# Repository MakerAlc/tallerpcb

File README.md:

# Taller de iniciación a los PCBs de MakerAlc
Repositorio del taller de iniciación a los PCBs impartido en MakerAlc.

En este repositorio se encuentran los archivos necesarios para el desarrollo de cada sesión.

Más información en https://sites.google.com/view/makealc/inicio

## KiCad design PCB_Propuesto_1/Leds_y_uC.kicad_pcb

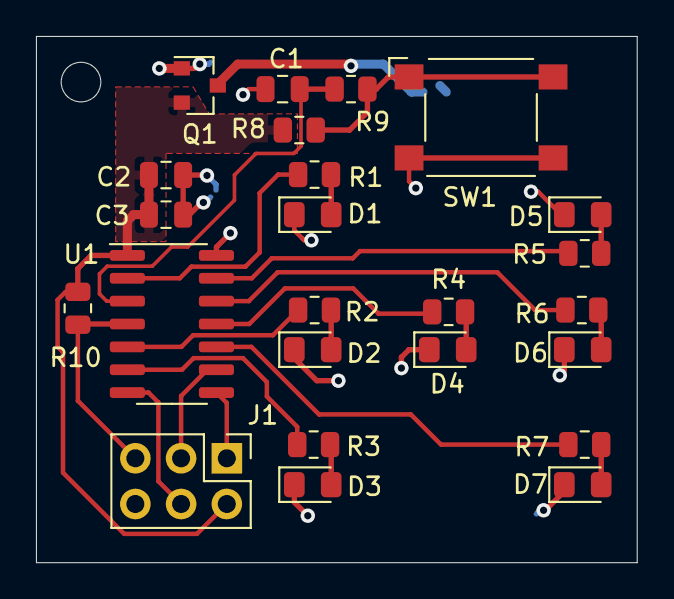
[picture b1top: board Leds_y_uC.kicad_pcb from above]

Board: 2 copper layers, 33.4 x 29.2 mm, 25 parts (1 on the bottom side), 23 nets.

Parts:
BT1: Battery_Cell; BatteryHolder_MPD_BC2003_1x2032
C1, C3: 100 nF; C_0805_2012Metric
C2: 10 uF; C_0805_2012Metric
D1, D2, D3, D4, D5, D6, D7: LED; LED_0805_2012Metric_Pad1.15x1.40mm_HandSolder
J1: AVR-ISP-6; PinHeader_2x03_P2.54mm_Vertical
Q1: Si2319CDS; SOT-23
R1, R2, R3, R4, R5, R6, R7, R9: 360; R_0805_2012Metric
R8, R10: 10K; R_0805_2012Metric
SW1: SW_MEC_5E; SW_SPST_Omron_B3FS-100xP
U1: ATtiny841-SSU; SOIC-14_3.9x8.7mm_P1.27mm

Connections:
GND: BT1.2, C1.2, C2.2, C3.2, D1.1, D2.1, D3.1, D4.1, D5.1, D6.1, D7.1, J1.6, Q1.1, SW1.3, SW1.4, U1.14
LED: R2.1, U1.5
MISO: J1.1, U1.8
MOSI: J1.4, U1.7
unnamed: BT1.1, Q1.3
unnamed: C1.1, R9.2, U1.3
unnamed: D1.2, R1.2
unnamed: D2.2, R2.2
unnamed: D3.2, R3.2
unnamed: D4.2, R4.2
unnamed: D5.2, R5.2
unnamed: D6.2, R6.2
unnamed: D7.2, R7.2
unnamed: R1.1, U1.2
unnamed: R3.1, U1.6
unnamed: R4.1, U1.11
unnamed: R5.1, U1.13
unnamed: R6.1, U1.12
unnamed: R7.1, U1.10
unnamed: R8.1, R9.1, SW1.1, SW1.2
RST: J1.5, R10.1, U1.4
SCK: J1.3, U1.9
VCC: C2.1, C3.1, J1.2, Q1.2, R8.2, R10.2, U1.1

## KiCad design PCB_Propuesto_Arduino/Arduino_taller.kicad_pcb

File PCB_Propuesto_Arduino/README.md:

# Taller_PCB_MakerAlc
Taller de iniciación a los PCBs

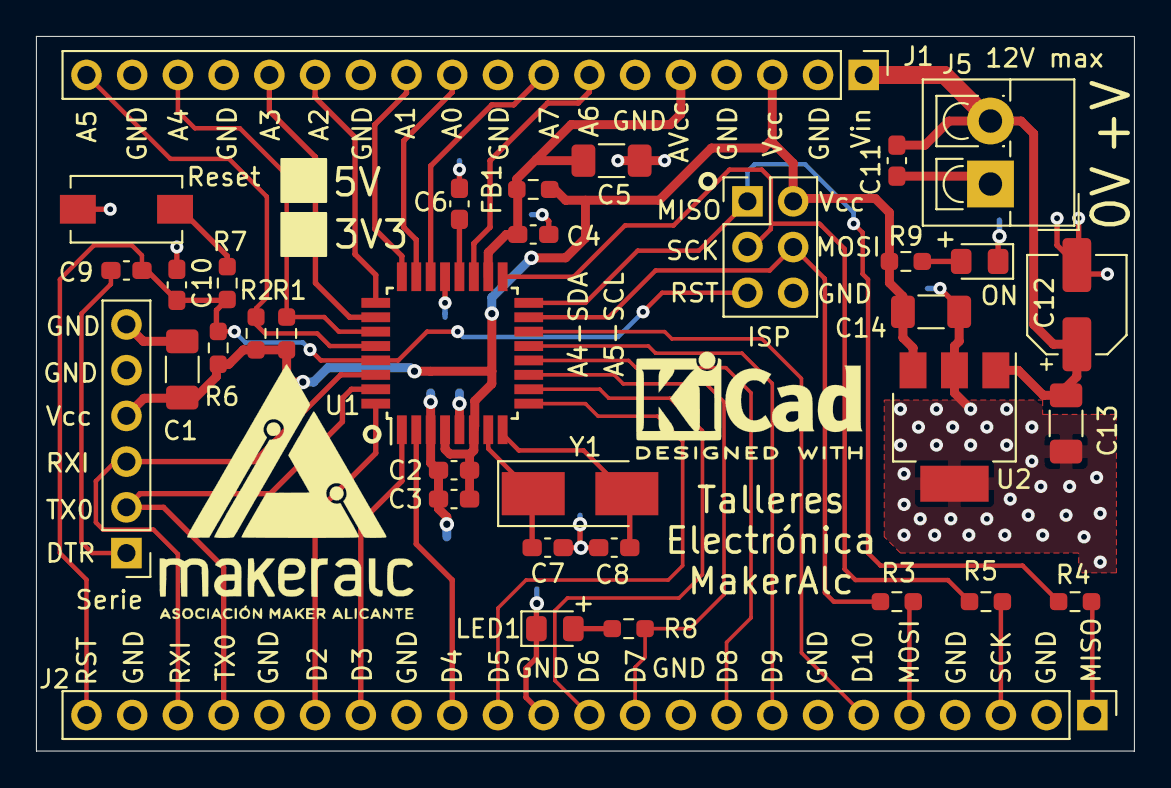
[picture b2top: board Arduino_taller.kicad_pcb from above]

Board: 2 copper layers, 61.0 x 39.7 mm, 35 parts (0 on the bottom side), 37 nets.

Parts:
C1, C5, C13, C14: 10 uF; C_1206_3216Metric_Pad1.33x1.80mm_HandSolder
C2, C3, C4, C6, C9, C11: 100 nF; C_0603_1608Metric_Pad1.08x0.95mm_HandSolder
C7, C8: 16 pF; C_0603_1608Metric_Pad1.08x0.95mm_HandSolder
C10: 10 nF; C_0603_1608Metric_Pad1.08x0.95mm_HandSolder
C12: DNP; CP_Elec_5x5.4
FB1: Ferrite_Bead_Small; R_0603_1608Metric_Pad0.98x0.95mm_HandSolder
ISP: AVR-ISP-6; PinHeader_2x03_P2.54mm_Vertical
J1: Conn_01x18; PinHeader_1x18_P2.54mm_Vertical
J2: Conn_01x23; PinHeader_1x23_P2.54mm_Vertical
J5: Screw_Terminal_01x02; TerminalBlock_4Ucon_1x02_P3.50mm_Vertical
LED1: LED; LED_0805_2012Metric_Pad1.15x1.40mm_HandSolder
ON: LED; LED_0805_2012Metric_Pad1.15x1.40mm_HandSolder
R1, R2: 4k7; R_0603_1608Metric_Pad0.98x0.95mm_HandSolder
R3, R4, R5, R8, R9: 1k; R_0603_1608Metric_Pad0.98x0.95mm_HandSolder
R6: 10k; R_0603_1608Metric_Pad0.98x0.95mm_HandSolder
R7: 100; R_0603_1608Metric_Pad0.98x0.95mm_HandSolder
Reset: SW_Push; SW_SPST_EVQPE1
Serie: FTDI Basic; PinHeader_1x06_P2.54mm_Vertical
U1: ATmega328P-AU; TQFP-32_7x7mm_P0.8mm
U2: MIC5239; SOT-223-3_TabPin2
Y1: 8 MHz; Crystal_SMD_5032-2Pin_5.0x3.2mm_HandSoldering

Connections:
A0: J1.10, U1.23
A1: J1.11, U1.24
A2: J1.13, U1.25
A3: J1.14, U1.26
A4: J1.16, R1.1, U1.27
A5: J1.18, R2.1, U1.28
A6: J1.7, U1.19
A7: J1.8, U1.22
AVcc: C4.1, C5.1, FB1.2, J1.5, U1.18
D2: J2.18, U1.32
D3: J2.17, U1.1
D4: J2.15, U1.2
D5: J2.14, U1.9
D6: J2.12, U1.10
D7: J2.11, R8.2, U1.11
D8: J2.9, U1.12
D9: J2.8, U1.13
D10: J2.6, U1.14
DTR: C9.1, Serie.1
GND: C1.2, C2.2, C3.2, C4.2, C5.2, C6.1, C7.1, C8.1, C10.1, C11.2, C12.2, C13.2, C14.2, ISP.6, J1.2, J1.4, J1.6, J1.9, J1.12, J1.15, J1.17, J2.2, J2.4, J2.7, J2.10, J2.13, J2.16, J2.19, J2.22, J5.1, LED1.1, ON.1, Reset.2, Serie.5, Serie.6, U1.3, U1.5, U1.21, U2.2
MISO: ISP.1, R4.1, U1.16
MOSI: ISP.4, R3.1, U1.15
unnamed: C6.2, U1.20
unnamed: C7.2, U1.7, Y1.1
unnamed: C8.2, U1.8, Y1.2
unnamed: LED1.2, R8.1
unnamed: ON.2, R9.1
unnamed: R7.1, Reset.1
RST: C9.2, C10.2, ISP.5, J2.23, R6.1, R7.2, U1.29
RXI: J2.21, Serie.3, U1.30
SCK: ISP.3, R5.1, U1.17
SPI_MISO: J2.1, R4.2
SPI_MOSI: J2.5, R3.2
SPI_SCK: J2.3, R5.2
TX0: J2.20, Serie.2, U1.31
VCC: C1.1, C2.1, C3.1, C14.1, FB1.1, ISP.2, J1.3, R1.2, R2.2, R6.2, R9.2, Serie.4, U1.4, U1.6, U2.3
Vin: C11.1, C12.1, C13.1, J1.1, J5.2, U2.1

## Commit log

2020-11-20 Añadido fichero de enlaces para el curso
2020-11-20 Nuevo enlace a canal ACadenas
2020-11-21 Añadidos enlaces a vídeos sobre electrónica
2020-11-21 Añadidos enlaces a vídeos sobre electrónica, texto corregido
2020-11-21 texto enlaces.txt corregido
2020-11-22 Resumen de lo hablado en la sesión 1 del taller de PCBs, completando información sobre el proyecto Arduino
2020-12-01 Añadido el guión de la sesión 2
2020-12-03 Añadida información sobre el taller
2020-12-07 .pdf con el esquema e imagen con los símbolos-huellas del PCB propuesto
2020-12-16 Añadido el guion de la sesión 3 del taller de iniciación a los PCBs
2020-12-19 pcb propuesto arduino, mandado a fabricar
2021-01-07 Añadido el guión para la sesión 4 del taller de PCBs
2021-03-23 añadidos gerbers dado y placa arduino
2021-11-30 Añadidos los gerbers del PCB y un BOM del taller de soldadura
